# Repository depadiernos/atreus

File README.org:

* Atreus Keyboard

The Atreus is a mechanical keyboard designed primarily to match the
shape of human hands and to be as portable as possible. The case
measures 26x12cm and lacks even a number row, relying heavily upon the
=fn= key. There is a circuit board for this design, but it's also
possible to [[http://wiki.geekhack.org/index.php?title=Hard-Wiring_How-To][manually wire the matrix]].

I've seen a number of existing DIY 40% keyboard designs, but most of
them stagger the rows, which I find very annoying now that I've gotten
used to the columnar layout of the [[https://geekhack.org/index.php?topic=22780.0][Ergodox]]. In addition, many of the
designs I've seen waste a lot of room on the space bar, failing to
take into account the fact that the thumb is the strongest and most
versatile of the fingers. This design avoids both these problems while
taking a more couch-friendly single-piece approach.

[[./atreus.jpg]]

See [[./changelog.md][the changelog]] for the various revisions made to the design since
its initial release.

** Kits

You can buy [[http://atreus.technomancy.us][Atreus kits]] that have all the parts you need along with
detailed assembly instructions from http://atreus.technomancy.us. If
you'd rather round up all the parts yourself, that's possible too
since the design is completely open source; see the bill of materials
below.

** Layout

Only a handful of punctuation marks (and no digits) are available
unshifted, and all the modifiers are on the bottom row:

 :    q     w     e     r     t       ||       y     u     i     o    p
 :    a     s     d     f     g       ||       h     j     k     l    ;
 :    z     x     c     v     b       ||       n     m     ,     .    /
 :   esc   tab  super shift bksp ctrl || alt space  fn     -     '  enter

The numbers and most of the punctuation are on the fn layer with a
numpad-style arrangement under the right hand:

 :    !    @     up     {    }        ||     pgup    7     8     9    *
 :    #  left   down  right  $        ||     pgdn    4     5     6    +
 :    [    ]      (     )    &        ||       `     1     2     3    \
 :   L2  insert super shift bksp ctrl || alt space   fn    .     0    =

The =L2= key switches it to the function layer, and tapping =L0= here
brings it back to the first layer.

 :  insert home    ↑    end  pgup     ||       ↑     F7    F8    F9   F10
 :    del   ←      ↓     →   pgdn     ||       ↓     F4    F5    F6   F11
 :                           reset    ||             F1    F2    F3   F12
 :              super shift bksp ctrl || alt space   L0             

The [[https://atreus.technomancy.us/download][firmware]] includes a number of other options, including
colemak and dvorak. [[https://atreus.technomancy.us/qmk][Customizing your layout]] is easy to do with the QMK configurator interface.

** Parts

*** Switches

This layout has five modifiers and 37 non-modifiers.

I strongly prefer the feel and sound of tactile [[https://deskthority.net/wiki/Matias_switch#Click][Matias Clicky]]
switches for typing. However, I like having [[https://deskthority.net/wiki/Matias_switch#Linear][Matias Linear
switches]] switches on the modifier keys (ctrl, alt, super, shift, and
fn) because the tactile effect has no benefit for keys that are held
down, and giving a different response helps you learn the layout more
quickly.

For users that need to operate in sound-sensitive environments like
open offices or libraries,
[[http://deskthority.net/wiki/Matias_switch#Quiet_click][Matias Quiet
Click]] switches are a popular choice since they still offer tactility
without the noise. Other users prefer switches in the
[[http://deskthority.net/wiki/Cherry_MX][Cherry MX]] family, which use
different keycaps and switch plates but still work fine.

*** Diodes

In order to avoid ghosting, each switch needs a diode. The [[https://www.radioshack.com/product/index.jsp?productId=2062587][1N4148]] is a
readily-available choice, but nearly any signal diode would work.

*** Microcontroller

The circuit board design uses a [[http://arduino.cc/en/Main/ArduinoBoardMicro][Arduino Pro Micro]].

Be sure to get a microcontroller without headers so it will fit in
between the bottom layer and the plate. USB micro is preferred over
USB mini for this reason as well.

*** Keycaps

Caps for Matias switches are included in the official kits. Sculpted
caps are also available [[http://matias.ca/order/#keycaps][from Matias]] or by harvesting from old Alps
keyboards. It's recommended that you use unlabeled keys, because due
to the different sizes and orientations of certain keys (backspace,
shift, enter, etc) many of the labels will be incorrect if present.

Cherry switches have more options. This
[[http://pimpmykeyboard.com/dsa-pbt-abs-blank-keycap-sets/][DSA-shaped base set]] (spherical indentations on the key, same profile for each
row) from Signature Plastics has 52 1x keys plus a few extras we won't
use. There are two "deep dish" keys in that set which you can place
under your index fingers on the home row to help guide your hands to
the right spot without looking. However, you only get a single 1.5x
keycap, and the middle two thumb keys both use them, so you might want
to pick up an extra.

** Circuit Board

The =atreus.rkt= program calculates switch and diode positions based
on row/column counts, spacing, and rotation factors, and emits a
=atreus.kicad_pcb= file. The board outline and traces are done by hand
and are stored in the =header.rktd= and =traces.rktd= files
respectively. The =atreus.kicad_pcb= file can be imported into [[http://kicad-pcb.org][Kicad]]
which can export Gerber files suitable for fabrication. A copy of the
Kicad PCB file is included in the repository if you don't want to
recompile it using Racket. Recompiling is only required if you want to
make changes to the procedurally-generated portions of the board.

Unfortunately most PCB fabricators require a minimum order of 10 or
so, making this impractical for one-offs. The PCB is not required, so
for one-off boards it's usually more sensible to stick with a [[http://atreus.technomancy.us/assembly-hand-wired.pdf][hand-wired build]] instead.

** Case

Layered laser-cut wood or acrylic. The [[http://geekhack.org/index.php?topic%3D54759.msg1304117#msg1304117][mark II case]] (EPS files in the
=case/= directory) features 8 screw holes and a kind of "stair step"
design around the top and bottom of the key clusters; mark I has
straight lines.

The files =alps-top-plate-3mm.eps=, =alps-switch-plate-3mm.eps=, and
=bottom-plate-3mm.eps= are to be cut in 3mm acrylic or wood. The
=spacer.eps= file can be cut on something thicker; between 4.5mm and
6mm is recommended. Alternatively you can cut it in 3mm twice. The
spacer needs to be at least as thick as the connector of the USB cable
you're using. If you are using Cherry switches, you should use
=cherry-3mm.eps= for the top, switch, and bottom plates instead, but
the spacer is the same.

There is also a programmatically-implemented version of the case
written in OpenSCAD; it is more flexible (you can tweak the number of
rows/cols, etc and recompile) but it doesn't match the canonical case
exactly; in particular the screw holes are placed differently.

The original case (=case-mk-i.svg=) design is also included; it is
slightly less wide and has a minor asymmetry with the screws on the
bottom side.

On a 100W Epilog laser, the 3mm layers cut in about a minute and a
half. I did a run with 6mm acrylic of the other layers which took
nearly 6 minutes.

Wood cases should be finished with sandpaper and lacquer, shellac, or polyurethane.

** Firmware

The [[https://qmk.fm][QMK firmware]] is
recommended. [[https://atreus.technomancy.us/download][Standard
layouts]] are available precompiled, or you can
[[https://atreus.technomancy.us/qmk][design your own]] in the
configurator.

There is also the older
[[https://github.com/technomancy/atreus-firmware][atreus-firmware]]
custom codebase which works but has fewer features. It is recommended
mostly for learning purposes since the code is much simpler and easier
to understand than QMK. Previously TMK was the recommended choice for
firmware, but QMK has much better documentation and ease of use and is
now recommended.

** Bill of Materials

If you don't want to get [[https://atreus.technomancy.us][the kit]] you can source parts yourself. (You
can also order a partial kit if you want to customize some of the
parts.) Using Cherry switches is cheapest unless you can find cheap
Alps-mount keycaps:

- 50 Matias or Cherry switches from mechanicalkeyboards.com
- 50 diodes from radio shack, ebay, or whatever
- 40 1x, 2 1.5x Keycaps from signatureplastics.com OR full keycap set from matias.ca
- A-star micro from pololu.com
- Case materials from various sources
- Case laser cutting: 7.5 minutes on a 100W Epilog laser; varies by source
- USB micro cable, get anywhere

Recommended but optional:

- 5 linear Matias or Cherry switches

The base keycap set from Signature Plastics only has one 1.5x key,
which is used for the inner thumb keys. You can use a 1x key for one
of them, but it looks kind of tacky, so I recommend getting a second
1.5x keycap separately.

*** Other Tools

You'll need a soldering iron, solder, and a wire cutter. A multimeter
can come in handy for testing the connections but is optional. You'll
also need eight M3 machine screws with nuts; the length of the screws
depends on the thickness of the acrylic you use. You can add rubber
feet to the bottom to prevent the board from sliding around when
placed on a desk. You'll also need sandpaper and lacquer for the
wooden case.

If you are building a hand-wired board you will also need a glue gun,
hookup wire, and wire strippers.

** Assembly

See the [[https://atreus.technomancy.us/assembly.pdf][assembly instructions]] PDF.

Hand-wired boards will want the [[https://atreus.technomancy.us/assembly-hand-wired.pdf][previous edition of the assembly instructions]].

The LaTeX source to the assembly instructions is in the =assembly= directory.

** Inspiration

These fine projects all provided inspiration for various aspects of
the Atreus, as well as the folks on the =#geekhack= freenode channel.

- [[https://geekhack.org/index.php?topic=22780.0][Ergodox]]
- [[http://deskthority.net/workshop-f7/onehand-20-keyboard-t6617.html][OneHand]]
- [[http://blog.fsck.com/2013/12/better-and-better-keyboards.html][keyboard.io]]
- [[http://geekhack.org/index.php?topic=48718][ErgoT]]

** Builds

If you've built an Atreus, please add your name to [[https://github.com/technomancy/atreus/wiki/BuildLogs][the build logs wiki]].

There's also a [[https://atreus.technomancy.us/list][mailing list]] for people who have built or ordered an
Atreus or are interested in doing so.

** Orestes

An [[https://www.flickr.com/photos/technomancy/14654421878][experimental build]] uses the [[http://pjrc.com/store/teensy31.html][Teensy 3]] microcontroller and
ARM [[https://github.com/technomancy/orestes/tree/teensy3][Forth-based]] firmware, but this is not really suitable for general-purpose use; it's more of a curiosity.

** License

Copyright © 2014-2018 Phil Hagelberg and contributors

Released under the [[https://www.gnu.org/licenses/gpl.html][GNU GPL version 3]]

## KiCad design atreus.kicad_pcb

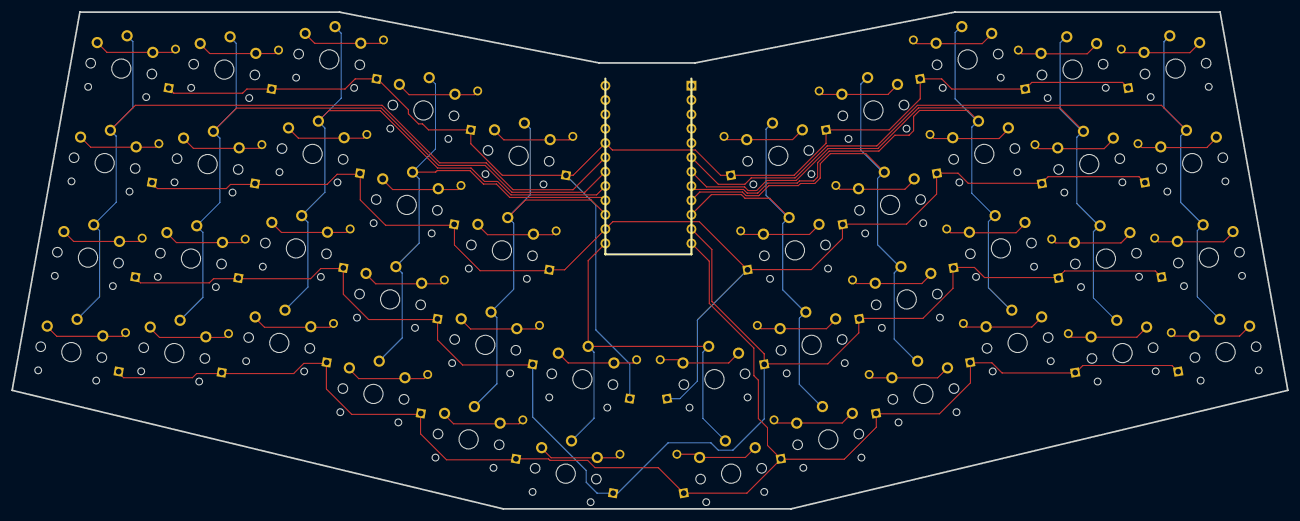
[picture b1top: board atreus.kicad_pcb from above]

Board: 2 copper layers, 226.0 x 88.0 mm, 89 parts (0 on the bottom side), 59 nets.

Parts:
D0:0, D0:1, D0:2, D0:3, D1:0, D1:1, D1:2, D1:3, D2:0, D2:1, D2:2, D2:3, D3:0, D3:1, D3:2, D3:3, D4:0, D4:1, D4:2, D4:3, D5:0, D5:1, D6:0, D6:1, D7:0, D7:1, D7:2, D7:3, D8:0, D8:1, D8:2, D8:3, D9:0, D9:1, D9:2, D9:3, D10:0, D10:1, D10:2, D10:3, D11:0, D11:1, D11:2, D11:3: DIODE
Promicro: PROMICRO
SW0:0, SW0:1, SW0:2, SW0:3, SW1:0, SW1:1, SW1:2, SW1:3, SW2:0, SW2:1, SW2:2, SW2:3, SW3:0, SW3:1, SW3:2, SW3:3, SW4:0, SW4:1, SW4:2, SW4:3, SW5:0, SW5:1, SW6:0, SW6:1, SW7:0, SW7:1, SW7:2, SW7:3, SW8:0, SW8:1, SW8:2, SW8:3, SW9:0, SW9:1, SW9:2, SW9:3, SW10:0, SW10:1, SW10:2, SW10:3, SW11:0, SW11:1, SW11:2, SW11:3: chocondiks

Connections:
N-col-0: Promicro.F5, SW0:0.1, SW0:1.1, SW0:2.1, SW0:3.1
N-col-1: Promicro.F6, SW1:0.1, SW1:1.1, SW1:2.1, SW1:3.1
N-col-2: Promicro.F7, SW2:0.1, SW2:1.1, SW2:2.1, SW2:3.1
N-col-3: Promicro.B1, SW3:0.1, SW3:1.1, SW3:2.1, SW3:3.1
N-col-4: Promicro.B3, SW4:0.1, SW4:1.1, SW4:2.1, SW4:3.1
N-col-5: Promicro.B6, SW5:0.1, SW5:1.1, SW6:0.1, SW6:1.1
N-col-6: Promicro.E6, SW7:0.1, SW7:1.1, SW7:2.1, SW7:3.1
N-col-7: Promicro.D7, SW8:0.1, SW8:1.1, SW8:2.1, SW8:3.1
N-col-8: Promicro.C6, SW9:0.1, SW9:1.1, SW9:2.1, SW9:3.1
N-col-9: Promicro.D4, SW10:0.1, SW10:1.1, SW10:2.1, SW10:3.1
N-col-10: Promicro.D0, SW11:0.1, SW11:1.1, SW11:2.1, SW11:3.1
N-diode-0: D0:0.1, SW0:0.2
N-diode-1: D0:1.1, SW0:1.2
N-diode-2: D0:2.1, SW0:2.2
N-diode-3: D0:3.1, SW0:3.2
N-diode-4: D1:0.1, SW1:0.2
N-diode-5: D1:1.1, SW1:1.2
N-diode-6: D1:2.1, SW1:2.2
N-diode-7: D1:3.1, SW1:3.2
N-diode-8: D2:0.1, SW2:0.2
N-diode-9: D2:1.1, SW2:1.2
N-diode-10: D2:2.1, SW2:2.2
N-diode-11: D2:3.1, SW2:3.2
N-diode-12: D3:0.1, SW3:0.2
N-diode-13: D3:1.1, SW3:1.2
N-diode-14: D3:2.1, SW3:2.2
N-diode-15: D3:3.1, SW3:3.2
N-diode-16: D4:0.1, SW4:0.2
N-diode-17: D4:1.1, SW4:1.2
N-diode-18: D4:2.1, SW4:2.2
N-diode-19: D4:3.1, SW4:3.2
N-diode-20: D5:0.1, SW5:0.2
N-diode-21: D5:1.1, SW5:1.2
N-diode-24: D6:0.1, SW6:0.2
N-diode-25: D6:1.1, SW6:1.2
N-diode-28: D7:0.1, SW7:0.2
N-diode-29: D7:1.1, SW7:1.2
N-diode-30: D7:2.1, SW7:2.2
N-diode-31: D7:3.1, SW7:3.2
N-diode-32: D8:0.1, SW8:0.2
N-diode-33: D8:1.1, SW8:1.2
N-diode-34: D8:2.1, SW8:2.2
N-diode-35: D8:3.1, SW8:3.2
N-diode-36: D9:0.1, SW9:0.2
N-diode-37: D9:1.1, SW9:1.2
N-diode-38: D9:2.1, SW9:2.2
N-diode-39: D9:3.1, SW9:3.2
N-diode-40: D10:0.1, SW10:0.2
N-diode-41: D10:1.1, SW10:1.2
N-diode-42: D10:2.1, SW10:2.2
N-diode-43: D10:3.1, SW10:3.2
N-diode-44: D11:0.1, SW11:0.2
N-diode-45: D11:1.1, SW11:1.2
N-diode-46: D11:2.1, SW11:2.2
N-diode-47: D11:3.1, SW11:3.2
N-row-0: D0:0.2, D1:0.2, D2:0.2, D3:0.2, D4:0.2, D5:0.2, D7:0.2, D8:0.2, D9:0.2, D10:0.2, D11:0.2, Promicro.F4
N-row-1: D0:1.2, D1:1.2, D2:1.2, D3:1.2, D4:1.2, D6:0.2, D7:1.2, D8:1.2, D9:1.2, D10:1.2, D11:1.2, Promicro.B2
N-row-2: D0:2.2, D1:2.2, D2:2.2, D3:2.2, D4:2.2, D5:1.2, D7:2.2, D8:2.2, D9:2.2, D10:2.2, D11:2.2, Promicro.B4
N-row-3: D0:3.2, D1:3.2, D2:3.2, D3:3.2, D4:3.2, D6:1.2, D7:3.2, D8:3.2, D9:3.2, D10:3.2, D11:3.2, Promicro.B5

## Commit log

2019-08-15 Some Changes:
    - Replaced Pololu A-Star with ProMicro.
    - Replaced switch footprint with Keebio's switch footprint.
    - Now supports MX, Alps, and Choc.
    - Replaced diode footprint with Keebio's switch footprint.
2019-08-15 brought that space back.
2019-08-16 starting to add some smd modules.
2019-08-20 added some modules.
2019-08-21 something else.
2019-08-21 added usb mini and crystal.
2019-08-21 miniusb, atmega, and crystal placements.
2019-08-21 added 0.1uf capacitors.
2019-08-21 completed the components.
2019-08-21 fuse.
2019-08-21 autorouting
2019-08-22 flipped promicro and routed the traces with auto-router.
2019-08-22 cases, i think.
2019-08-25 manual route.
2019-08-26 manual routing. again.
2019-08-26 lowered promicro and manual routing again.
2019-08-27 modified case.
2019-08-28 manually traced the thing.
2019-08-29 hand routing, again.
2019-08-29 hand routing, again. again.
2019-08-30 cosmetics.
2019-09-03 promicro, trace, and revision.
2019-09-03 new branch, only chocs.
2019-09-03 case for choc.
2019-09-04 removed choc support.
2019-09-04 changed the footprint
2019-09-04 changed again.
2019-10-01 changed the measurements.
    - switch module should starts at 7, not 6.35. because 14mm.
    - add 0.2mm separation for a more fitting holes.
2019-10-01 forgot to add bottom case.
2019-10-10 make space.
2019-10-10 44 keys.
2019-10-11 smaller bezel, i guess.
2019-10-17 removed the screw holes next to usb cable.
2019-10-21 added csv.
2019-12-11 updated readme.
2019-12-11 52 keys.
2019-12-13 aoeuaoeu
2019-12-14 62 keys.
2020-01-23 3d cases.
2020-02-03 pcb is too tight in a case.
2020-02-06 added wrist-rest.
2020-02-23 still the same as usual. changed some measurements.
2020-02-28 stacked thing.
2020-06-02 rotated the diode's leg holes. i'm dumb, i know.
2020-06-03 cleaned up.:
2020-06-04 cosmetic changes on the tracks.
2020-08-29 chocondiks

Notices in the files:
atreus.kicad_pcb:
GPLv3
